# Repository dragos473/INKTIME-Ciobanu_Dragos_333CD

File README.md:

# InkTime – Smartwatch Open Source

InkTime este un smartwatch open-source construit in jurul microcontroller-ului nRF52840. Are display e-paper de 1.54", feedback haptic, si incarcare prin USB-C.

## Diagrama Bloc

```
                         +-----------+
        USB-C ──VBUS──>──| BQ25180   |──VBAT──>──[ Baterie LiPo ]
        (J3)             | (Charger) |              |
          |              +-----------+               |
          |                   |                      |
          |                   v                      v
          |              +-----------+         +-----------+
          |              | RT6160A   |<──VREG──| MAX17048  |
          |              | (DC/DC)   |         | (Fuel     |
          |              +-----------+         |  Gauge)   |
          |                   |                +-----------+
          |                 3V3                      |
          |                   |                   ALERT
          v                   v                      |
     +--------------------------------------------+  |
     |               nRF52840                      |<-+
     |                                             |
     |   SPI ──> Display E-Paper (conector FPC J2) |
     |   I2C ──> BMA423 (IMU)                      |
     |   I2C ──> DRV2605 (Haptic Driver)           |
     |   I2C ──> BQ25180 / RT6160A / MAX17048      |
     |   GPIO ──> 3x Butoane (UP/ENTER/DOWN)       |
     |   USB ──> USB-C (D+/D-)                     |
     |   RF ──> Antena 2.4GHz (BLE)                |
     +---------------------------------------------+
```

## Descriere Hardware

### Microcontroller – nRF52840

nRF52840 e IC-ul principal al proiectului. E un SoC cu procesor Cortex-M4F, are 1MB flash si 256kB RAM si merge pana la 64MHz. Suporta BLE 5.0 si USB 2.0. Toate perifericele de pe placa comunica cu el prin I2C, SPI sau GPIO.

### Alimentare

Lantul de alimentare arata asa: USB-C (VBUS, 5V) → BQ25180 (incarcator LiPo) → baterie LiPo (VBAT) → RT6160A (convertor DC/DC buck-boost) → linia de 3V3.

### Display E-Paper

Display-ul se conecteaza printr-un conector FPC cu 24 de pini. Circuitul de drive pentru e-paper foloseste un boost converter ca sa genereze tensiunile mari (PREVGH si PREVGL) de care are nevoie panoul. Un P-MOSFET (DMG2305UX) controlat de pinul P1.01 porneste/opreste alimentarea circutului de display, ca sa poata fi oprit complet cand nu se face refresh.

Semnalele SPI (SCK, MOSI, CS) si GPIO-urile de control (DC, RST, BUSY) merg direct la nRF52840. Fiecare linie de tensiune mare are condensatoare de decuplare de 1µF/50V.

### IMU – BMA423

BMA423 e un accelerometru triaxial folosit pentru numararea pasilor si detectarea gesturilor. Comunica pe I2C. Pinul SDO e legat la GND printr-un rezistor de 0Ω (R3), ceea ce seteaza adresa I2C la 0x18. CSB e legat la VDD ca sa selecteze modul I2C. INT1 si INT2 merg la nRF52840 pentru interrupt-uri.

### Haptic Driver – DRV2605

DRV2605 controleaza un motor LRA/ERM pentru feedback haptic. E controlat prin I2C si activat prin GPIO (P0.12 → EN). Pinul IN/TRIG e legat la GND (nu se foloseste in modul I2C). OUT+ si OUT- se conecteaza la motor prin test pad-uri.

### USB-C si Protectie ESD

Conectorul USB-C (KH-TYPE-C-16P) furnizeaza alimentare (VBUS) si date (D+, D-). Doua rezistoare de 5.1kΩ pe CC1 si CC2 identifica dispozitivul ca UFP (sink). USBLC6-2SC6Y asigura protectie ESD pe liniile de date. D+/D- se conecteaza la controller-ul USB intern al nRF52840.

### Butoane

Trei butoane tactile (EVP-AKE31A): UP (P0.13), ENTER (P0.14), DOWN (P1.02). Fiecare buton are un pull-up de 10kΩ la 3V3 si un condensator de debounce de 1µF la GND. Cand e apasat, butonul trage pinul la GND (active-low).

### Debug SWD

Un footprint TC2030-IDC (tag-connect) ofera acces SWD (SWDIO, SWDCLK, RESET, VCC, GND). Pe placa sunt si test pad-uri pentru SWO, SWDIO, SWDCLK, RESET, 3V3 si GND.

### Magistrala I2C

Toate perifericele I2C sunt pe acelasi bus, pe pinii P0.06 (SDA) si P0.07 (SCL). Rezistoarele de pull-up sunt de 3.3kΩ, conectate la 3V3.

| Dispozitiv | Adresa I2C | Functie |
|------------|------------|---------|
| BQ25180 | 0x6A | Incarcator baterie |
| RT6160A | 0x75 | Convertor DC/DC |
| MAX17048 | 0x36 | Fuel gauge |
| BMA423 | 0x18 | Accelerometru |
| DRV2605 | 0x5A | Driver haptic |

## Pinii nRF52840

| Pin | Pad | Semnal | Descriere |
|-----|-----|--------|-----------|
| P0.00 | D2 | XL1 | Intrare cristal 32.768kHz |
| P0.01 | F2 | XL2 | Iesire cristal 32.768kHz |
| P0.02 | A12 | SCK | SPI clock catre display e-paper |
| P0.03 | B13 | MOSI | SPI data catre display e-paper |
| P0.05 | K2 | EPD_CS | SPI chip select pentru display |
| P0.06 | L1 | SDA | I2C data (bus comun) |
| P0.07 | M2 | SCL | I2C clock (bus comun) |
| P0.08 | N1 | IMU_INT1 | Interrupt 1 de la BMA423 |
| P0.10 | J24 | ALERT | Alerta baterie de la MAX17048 |
| P0.11 | T2 | PMIC_INT | Interrupt de la BQ25180 |
| P0.12 | U1 | HAPTIC_EN | Enable pentru DRV2605 |
| P0.13 | AD8 | BTN_UP | Buton UP (active-low) |
| P0.14 | AC9 | BTN_ENTER | Buton ENTER (active-low) |
| P0.15 | AD10 | EPD_DC | Data/Command pentru display |
| P0.16 | AC11 | EPD_RST | Reset display e-paper |
| P0.17 | AD12 | EPD_BUSY | Busy flag display e-paper |
| P0.18 | AC13 | RESET | Reset sistem |
| P1.00 | AD22 | SWO | Serial Wire Output (debug) |
| P1.01 | Y23 | PWR_EPD | Gate MOSFET alimentare display |
| P1.02 | W24 | BTN_DOWN | Buton DOWN (active-low) |
| P1.08 | P2 | IMU_INT2 | Interrupt 2 de la BMA423 |
| AD2 | — | VBUS | Detectie USB VBUS |
| AD4 | — | D- | USB data minus |
| AD6 | — | D+ | USB data plus |
| AA24 | — | SWDCLK | SWD clock (debug) |
| AC24 | — | SWDIO | SWD data (debug) |
| XC1/B24 | — | XC1 | Intrare cristal 32MHz |
| XC2/A23 | — | XC2 | Iesire cristal 32MHz |
| H23 | — | ANT | Iesire RF catre antena |
| W1, B1, A22, AD14, AD23 | — | VDD | Alimentare 3.3V |
| Y2 | — | VDDH | Alimentare 3.3V (high-voltage) |
| B7, F23 | — | VSS/GND | Masa |

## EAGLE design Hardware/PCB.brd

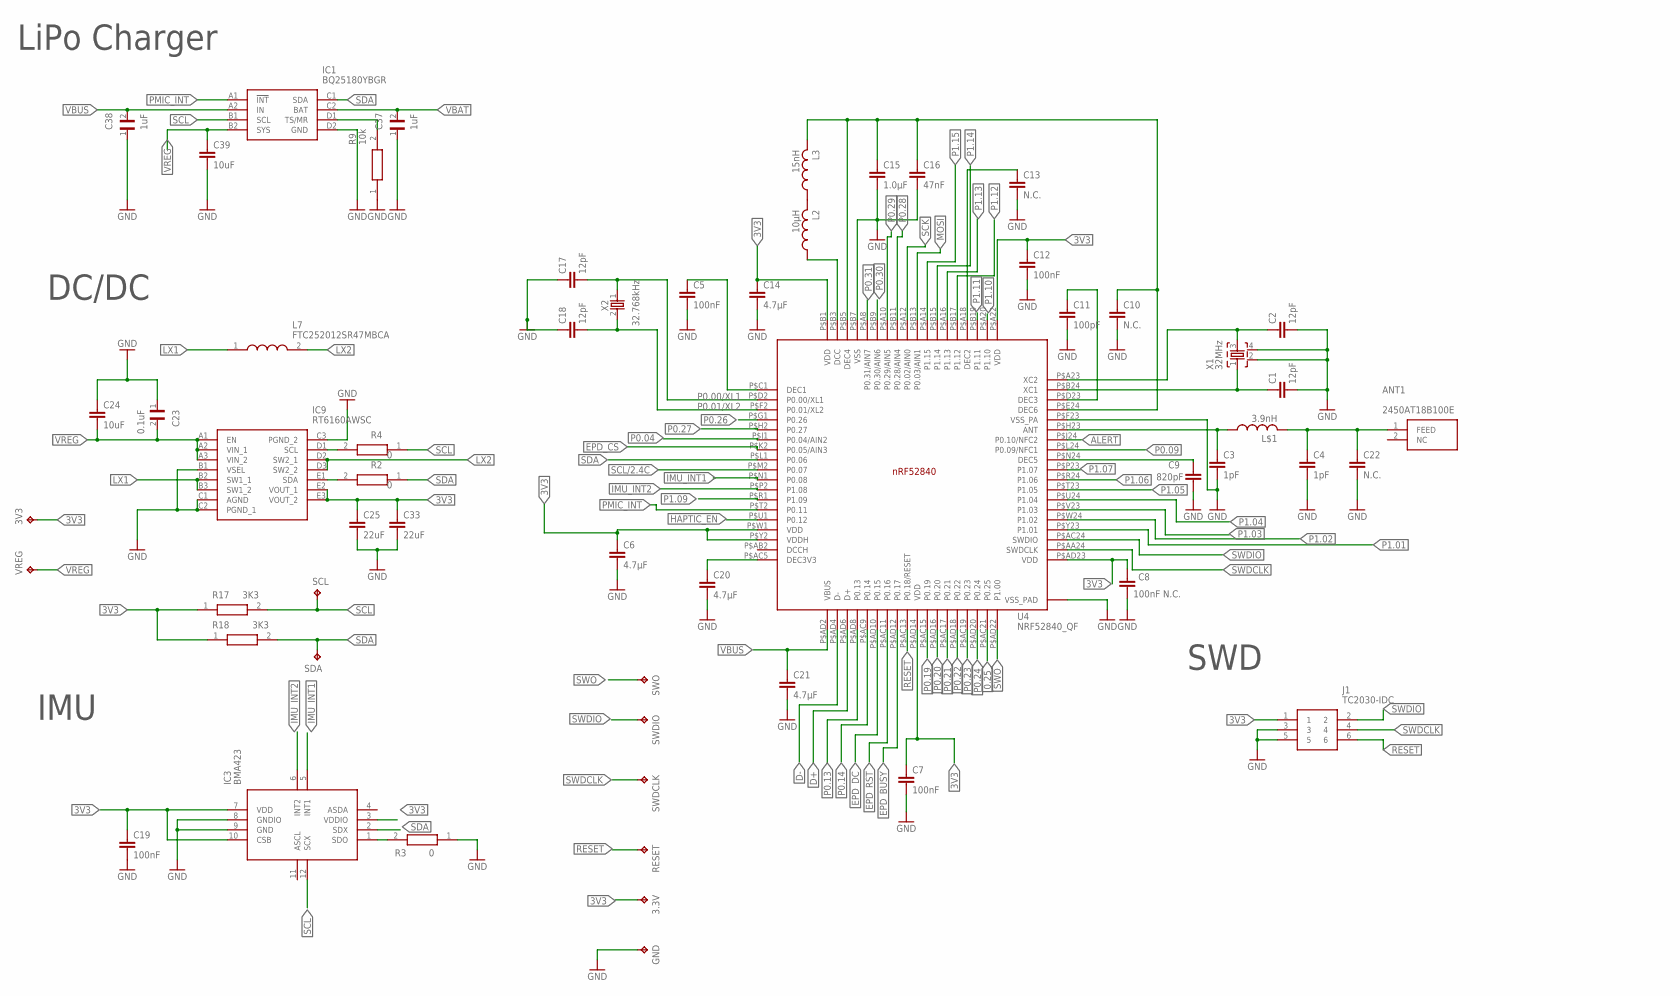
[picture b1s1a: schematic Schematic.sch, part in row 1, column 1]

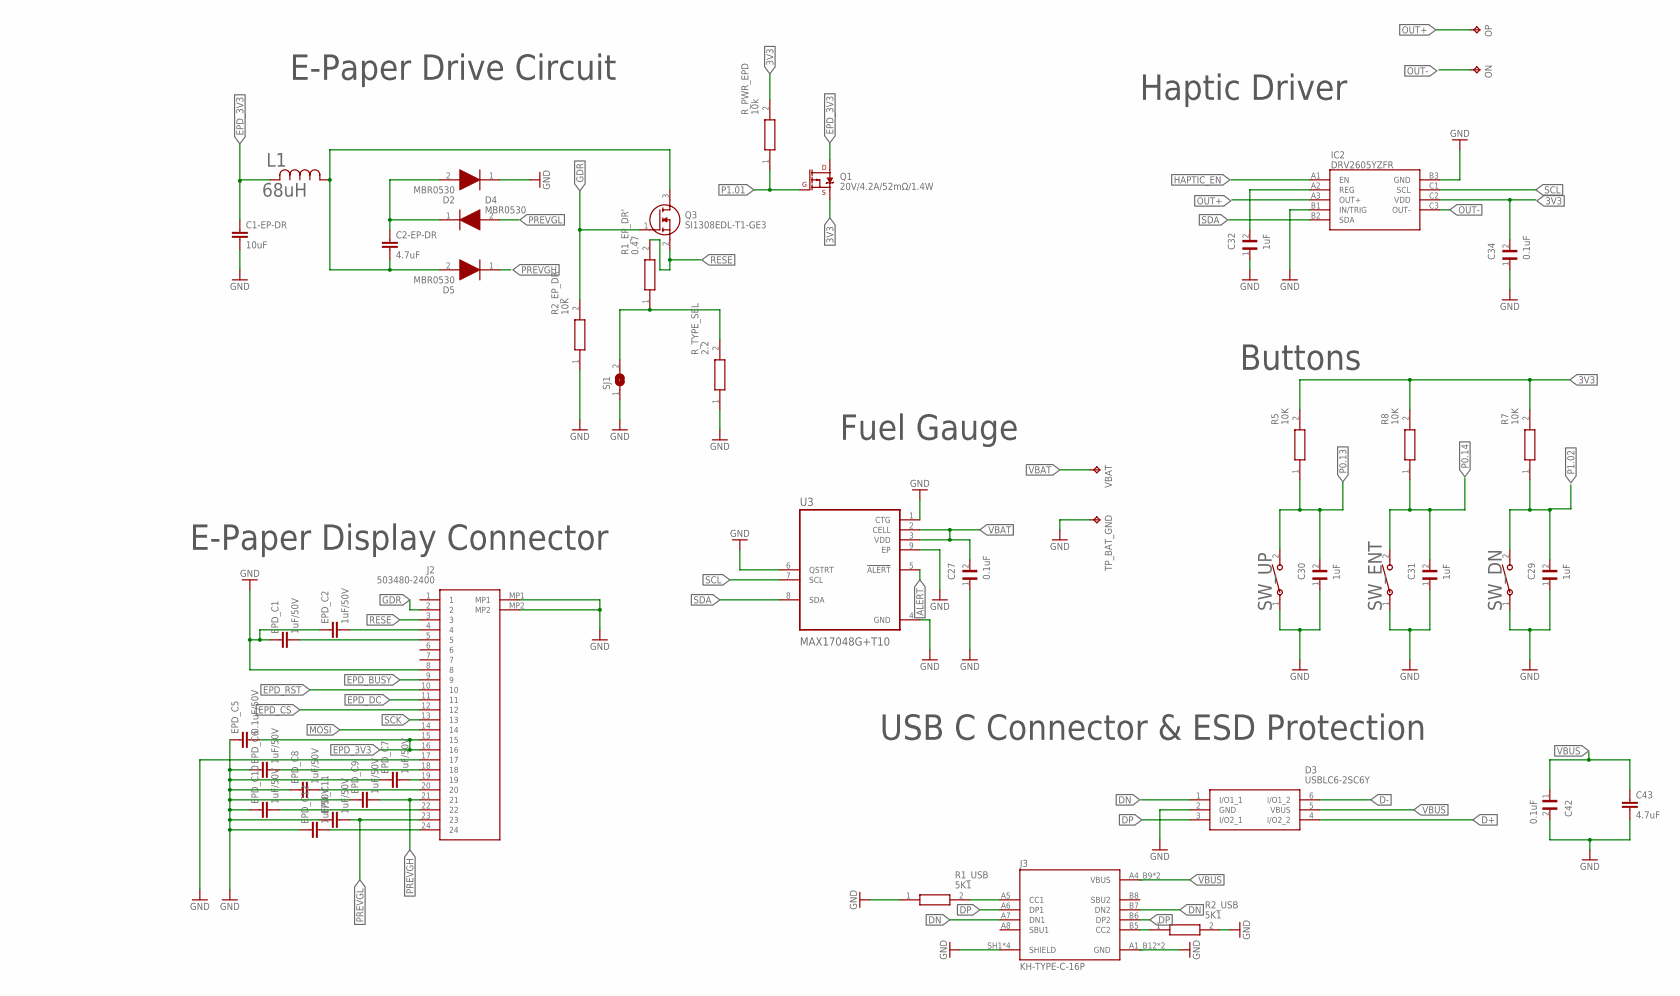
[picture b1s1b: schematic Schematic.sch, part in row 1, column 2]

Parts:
3.3V, 3V3: HECTOR_WATCH_1_TPTP20R; HECTOR_WATCH_1_TP20R
ANT1: 2450AT18B100E; 2450AT18B100E_ANTC3216X140N
C1, C2, C17, C18: 12pF; NORDIC_NRF_3_RESC0201_L
C1-EP-DR, C24, C39: 10uF; NORDIC_NRF_3_RESC0201_L
C2-EP-DR, C43: 4.7uF; NORDIC_NRF_3_RESC0201_L
C3, C4: 1pF; NORDIC_NRF_3_RESC0201_L
C5, C7, C12, C19: 100nF; NORDIC_NRF_3_RESC0201_L
C6, C14, C20, C21: 4.7μF; NORDIC_NRF_3_RESC0201_L
C8: 100nF N.C.; NORDIC_NRF_3_RESC0201_L
C9: 820pF; NORDIC_NRF_3_RESC0201_L
C10, C13, C22: N.C.; NORDIC_NRF_3_RESC0201_L
C11: 100pF; NORDIC_NRF_3_RESC0201_L
C15: 1.0μF; NORDIC_NRF_3_RESC0201_L
C16: 47nF; NORDIC_NRF_3_RESC0201_L
C23, C27, C34, C42: 0.1uF; GRM011R60J152KE01L_2_CAPC0201X13N
C25, C33: 22uF; NORDIC_NRF_3_RESC0201_L
C29, C30, C31, C32, C37, C38: 1uF; GRM011R60J152KE01L_2_CAPC0201X13N
D2, D4, D5: MBR0530; ESP32_C6_LIBRARY_5_SOD3716X135N
D3: USBLC6-2SC6Y; ESP32_C6_LIBRARY_3_SOT95P280X145-6N
EPD_C1, EPD_C2, EPD_C6, EPD_C7, EPD_C8, EPD_C9, EPD_C10, EPD_C11, EPD_C12: 1uF/50V; NORDIC_NRF_3_RESC0201_L
EPD_C5: 0.1uF/50V; NORDIC_NRF_3_RESC0201_L
GND: HECTOR_WATCH_1_TPTP20R; HECTOR_WATCH_1_TP20R
IC1: BQ25180YBGR; BQ25180YBGR_BGA8C40P2X4_100X155X50
IC2: DRV2605YZFR; DRV2605YZFR_BGA9C50P3X3_144X144X62
IC3: BMA423; BMA423_BMA423
IC9: RT6160AWSC; RT6160AWSC_BGA15C40P3X5_140X230X60
J1: TC2030-IDC; TC2030-IDC_TC2030IDC
J2: 503480-2400; 503480-2400_5034802400
J3: KH-TYPE-C-16P; KH-TYPE-C-16P_KINGHELM_KH-TYPE-C-16P
L1: 68uH; ESP32_C6_LIBRARY_2_IND_4828-WE-TPC_WRE
L2: 10μH; NORDIC_NRF_2_RESC0201_L
L3: 15nH; NORDIC_NRF_2_RESC0201_L
L7: FTC252012SR47MBCA; MLP2016SR47MT0S1_INDC2016X100N
L$1: 3.9nH; NORDIC_NRF_2_RESC0402_L
ON: HECTOR_WATCH_1_TPTP20R; HECTOR_WATCH_1_TP20R
OP: HECTOR_WATCH_1_TPTP20R; HECTOR_WATCH_1_TP20R
Q1: 20V/4.2A/52mΩ/1.4W; ESP32_C6_LIBRARY_4_ESP32_C6_LIBRARY_4_ESP32_C6_LIBRARY_4_ES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
Q3: SI1308EDL-T1-GE3; ESP32_C6_LIBRARY_6_SOT65P210X110-3N
R1_EP_DR': 0.47; ERA-1AEB3401C_0201
R1_USB, R2_USB: 5K1; ERA-1AEB3401C_0201
R2, R3, R4: 0; ERA-1AEB3401C_0201
R2_EP_DR, R5, R7, R8: 10K; ERA-1AEB3401C_0201
R9: 10k; CPF0201D7K68C1_0201
R17, R18: 3K3; ERA-1AEB3401C_0201
RESET: HECTOR_WATCH_1_TPTP20R; HECTOR_WATCH_1_TP20R
R_PWR_EPD: 10k; ERA-1AEB3401C_0201
R_TYPE_SEL: 2.2; ERA-1AEB3401C_0201
SCL: HECTOR_WATCH_1_TPTP20R; HECTOR_WATCH_1_TP20R
SDA: HECTOR_WATCH_1_TPTP20R; HECTOR_WATCH_1_TP20R
SJ1: ESP32_C6_LIBRARY_7_JUMPER_SJ
SWDCLK: HECTOR_WATCH_1_TPTP20R; HECTOR_WATCH_1_TP20R
SWDIO: HECTOR_WATCH_1_TPTP20R; HECTOR_WATCH_1_TP20R
SWO: HECTOR_WATCH_1_TPTP20R; HECTOR_WATCH_1_TP20R
SW_DN: 2025-10-22_07-23-44_LIBRARY_EVP-AKE31ASW_EVP-AKE3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; 2025-10-22_07-23-44_LIBRARY_SW_EVP-AKE31A_PAN
SW_ENT: 2025-10-22_07-23-44_LIBRARY_EVP-AKE31ASW_EVP-AKE3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; 2025-10-22_07-23-44_LIBRARY_SW_EVP-AKE31A_PAN
SW_UP: 2025-10-22_07-23-44_LIBRARY_EVP-AKE31ASW_EVP-AKE3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; 2025-10-22_07-23-44_LIBRARY_SW_EVP-AKE31A_PAN
TP_BAT_GND: HECTOR_WATCH_1_TPTP20R; HECTOR_WATCH_1_TP20R
U3: MAX17048G+T10; ESP32_C6_LIBRARY_SON50P200X200X80-9N
U4: NRF52840_QF; NORDIC_NRF_4_AQFN50P700X700X85_HS-74N
VBAT: HECTOR_WATCH_1_TPTP20R; HECTOR_WATCH_1_TP20R
VREG: HECTOR_WATCH_1_TPTP20R; HECTOR_WATCH_1_TP20R
X1: 32MHz; NORDIC_NRF_BT-XTAL_2016_N
X2: 32.768kHz; NORDIC_NRF_1_XTAL_3215_N

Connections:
0.25: U4.P$AC21 (P0.25)
3V3: 3.3V.TP, 3V3.TP, C6.1, C7.1, C8.1, C12.1, C14.1, C19.1, C25.1, C33.1, C34.2, IC2.C2 (VDD), IC3.3 (VDDIO), IC3.7 (VDD), IC3.10 (CSB), IC9.E2 (VOUT_1), IC9.E3 (VOUT_2), J1.1, Q1.2 (S), R5.2, R7.2, R8.2, R17.1, R18.1, R_PWR_EPD.2, U4.P$A22 (VDD), U4.P$AD14 (VDD), U4.P$AD23 (VDD), U4.P$B1 (VDD), U4.P$W1 (VDD), U4.P$Y2 (VDDH)
ALERT: U3.5 (!ALERT), U4.P$J24 (P0.10/NFC2)
D+: D3.4 (I/O2_2), U4.P$AD6 (D+)
D-: D3.6 (I/O1_2), U4.P$AD4 (D-)
DN: D3.1 (I/O1_1), J3.A7 (DN1), J3.B7 (DN2)
DP: D3.3 (I/O2_1), J3.A6 (DP1), J3.B6 (DP2)
EPD_3V3: C1-EP-DR.1, EPD_C5.2, J2.15, J2.16, L1.2, Q1.3 (D)
EPD_BUSY: J2.9, U4.P$AD12 (P0.17)
EPD_CS: J2.12, U4.P$K2 (P0.05/AIN3)
EPD_DC: J2.11, U4.P$AD10 (P0.15)
EPD_RST: J2.10, U4.P$AC11 (P0.16)
GDR: J2.2, Q3.1 (G), R2_EP_DR.2
GND: C1.2, C1-EP-DR.2, C2.2, C3.2, C4.2, C5.2, C6.2, C7.2, C8.2, C9.2, C10.2, C11.2, C12.2, C13.2, C14.2, C15.2, C16.2, C17.1, C18.1, C19.2, C20.2, C21.2, C22.2, C23.1, C24.1, C25.2, C27.1, C29.1, C30.1, C31.1, C32.1, C33.2, C34.1, C37.1, C38.1, C39.2, C42.2, C43.2, D2.1 (K), D3.2 (GND), EPD_C1.1, EPD_C2.1, EPD_C5.1, EPD_C6.1, EPD_C7.1, EPD_C8.1, EPD_C9.1, EPD_C10.1, EPD_C11.1, EPD_C12.1, GND.TP, IC1.D2 (GND), IC2.B1 (IN/TRIG), IC2.B3 (GND), IC3.8 (GNDIO), IC3.9 (GND), IC9.B1 (VSEL), IC9.C1 (AGND), IC9.C2 (PGND_1), IC9.C3 (PGND_2), J1.3, J1.5, J2.8, J2.17, J2.MP1, J2.MP2, J3.A1_B12 (GND), J3.A12_B1 (GND), J3.SH1 (SHIELD), J3.SH2 (SHIELD), J3.SH3 (SHIELD), J3.SH4 (SHIELD), R1_USB.1, R2_EP_DR.1, R2_USB.2, R3.1, R9.1, R_TYPE_SEL.1, SJ1.1, SW_DN.1, SW_ENT.1, SW_UP.1, TP_BAT_GND.TP, U3.1 (CTG), U3.4 (GND), U3.6 (QSTRT), U3.9 (EP), U4.P$74 (VSS_PAD), U4.P$75 (VSS_PAD), U4.P$76 (VSS_PAD), U4.P$77 (VSS_PAD), U4.P$78 (VSS_PAD), U4.P$79 (VSS_PAD), U4.P$80 (VSS_PAD), U4.P$81 (VSS_PAD), U4.P$82 (VSS_PAD), U4.P$83 (VSS_PAD), U4.P$84 (VSS_PAD), U4.P$85 (VSS_PAD), U4.P$86 (VSS_PAD), U4.P$87 (VSS_PAD), U4.P$88 (VSS_PAD), U4.P$89 (VSS_PAD), U4.P$90 (VSS_PAD), U4.P$B7 (VSS), U4.P$F23 (VSS_PA), X1.2, X1.4
HAPTIC_EN: IC2.A1 (EN), U4.P$U1 (P0.12)
IMU_INT1: IC3.5 (INT1), U4.P$N1 (P0.08)
IMU_INT2: IC3.6 (INT2), U4.P$P2 (P1.08)
LX1: IC9.B2 (SW1_1), IC9.B3 (SW1_2), L7.1
LX2: IC9.D2 (SW2_1), IC9.D3 (SW2_2), L7.2
MOSI: J2.14, U4.P$B13 (P0.03/AIN1)
unnamed: IC1.D1 (TS/MR), R9.2
unnamed: IC9.D1 (SCL), R4.2
unnamed: IC9.E1 (SDA), R2.2
unnamed: C5.1, U4.P$C1 (DEC1)
unnamed: C20.1, U4.P$AC5 (DEC3V3)
unnamed: C9.1, U4.P$N24 (DEC5)
unnamed: C3.1, L$1.1, U4.P$H23 (ANT)
unnamed: ANT1.1 (FEED), C4.1, C22.1, L$1.2
unnamed: C2.1, U4.P$A23 (XC2), X1.3
unnamed: C1.1, U4.P$B24 (XC1), X1.1
unnamed: C10.1, C15.1, C16.1, L3.2, U4.P$B5 (DEC4), U4.P$E24 (DEC6)
unnamed: C11.1, U4.P$D23 (DEC3)
unnamed: C13.1, U4.P$A18 (DEC2)
unnamed: L2.2, L3.1
unnamed: L2.1, U4.P$B3 (DCC)
unnamed: IC3.1 (SDO), R3.2
unnamed: C2-EP-DR.2, D5.2 (A), L1.1, Q3.3 (D)
unnamed: C2-EP-DR.1, D2.2 (A), D4.1 (K)
unnamed: R1_EP_DR'.1, R_TYPE_SEL.2, SJ1.2
unnamed: C32.2, IC2.A2 (REG)
unnamed: EPD_C2.2, J2.4
unnamed: EPD_C1.2, J2.5
unnamed: EPD_C6.2, J2.18
unnamed: EPD_C7.2, J2.19
unnamed: EPD_C8.2, J2.20
unnamed: EPD_C10.2, J2.22
unnamed: EPD_C12.2, J2.24
unnamed: J3.B5 (CC2), R2_USB.1
unnamed: J3.A5 (CC1), R1_USB.2
OUT+: IC2.A3 (OUT+), OP.TP
OUT-: IC2.C3 (OUT-), ON.TP
P0.00/XL1: C17.2, U4.P$D2 (P0.00/XL1), X2.1
P0.01/XL2: C18.2, U4.P$F2 (P0.01/XL2), X2.2
P0.04: U4.P$J1 (P0.04/AIN2)
P0.09: U4.P$L24 (P0.09/NFC1)
P0.13: C30.2, R5.1, SW_UP.2, U4.P$AD8 (P0.13)
P0.14: C31.2, R8.1, SW_ENT.2, U4.P$AC9 (P0.14)
P0.19: U4.P$AC15 (P0.19)
P0.20: U4.P$AD16 (P0.20)
P0.21: U4.P$AC17 (P0.21)
P0.22: U4.P$AD18 (P0.22)
P0.23: U4.P$AC19 (P0.23)
P0.24: U4.P$AD20 (P0.24)
P0.26: U4.P$G1 (P0.26)
P0.27: U4.P$H2 (P0.27)
P0.28: U4.P$B11 (P0.28/AIN4)
P0.29: U4.P$A10 (P0.29/AIN5)
P0.30: U4.P$B9 (P0.30/AIN6)
P0.31: U4.P$A8 (P0.31/AIN7)
P1.01: Q1.1 (G), R_PWR_EPD.1, U4.P$Y23 (P1.01)
P1.02: C29.2, R7.1, SW_DN.2, U4.P$W24 (P1.02)
P1.03: U4.P$V23 (P1.03)
P1.04: U4.P$U24 (P1.04)
P1.05: U4.P$T23 (P1.05)
P1.06: U4.P$R24 (P1.06)
P1.07: U4.P$P23 (P1.07)
P1.09: U4.P$R1 (P1.09)
P1.10: U4.P$A20 (P1.10)
P1.11: U4.P$B19 (P1.11)
P1.12: U4.P$B17 (P1.12)
P1.13: U4.P$A16 (P1.13)
P1.14: U4.P$B15 (P1.14)
P1.15: U4.P$A14 (P1.15)
PMIC_INT: IC1.A1 (!INT), U4.P$T2 (P0.11)
PREVGH: D5.1 (K), EPD_C9.2, J2.21
PREVGL: D4.2 (A), EPD_C11.2, J2.23
RESE: J2.3, Q3.2 (S), R1_EP_DR'.2
RESET: J1.6, RESET.TP, U4.P$AC13 (P0.18/RESET)
SCK: J2.13, U4.P$A12 (P0.02/AIN0)
SCL: IC1.B1 (SCL), IC2.C1 (SCL), IC3.12 (SCX), R4.1, R17.2, SCL.TP, U3.7 (SCL)
SCL/2.4C: U4.P$M2 (P0.07)
SDA: IC1.C1 (SDA), IC2.B2 (SDA), IC3.2 (SDX), R2.1, R18.2, SDA.TP, U3.8 (SDA), U4.P$L1 (P0.06)
SWDCLK: J1.4, SWDCLK.TP, U4.P$AA24 (SWDCLK)
SWDIO: J1.2, SWDIO.TP, U4.P$AC24 (SWDIO)
SWO: SWO.TP, U4.P$AD22 (P1.00)
VBAT: C27.2, C37.2, IC1.C2 (BAT), U3.2 (CELL), U3.3 (VDD), VBAT.TP
VBUS: C21.1, C38.2, C42.1, C43.1, D3.5 (VBUS), IC1.A2 (IN), J3.A4_B9 (VBUS), J3.A9_B4 (VBUS), U4.P$AD2 (VBUS)
VREG: C23.2, C24.2, C39.1, IC1.B2 (SYS), IC9.A1 (EN), IC9.A2 (VIN_1), IC9.A3 (VIN_2), VREG.TP

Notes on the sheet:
LiPo Charger
DC/DC
IMU
SWD
E-Paper Drive Circuit
E-Paper Display Connector
Fuel Gauge
Haptic Driver
Buttons
USB C Connector & ESD Protection

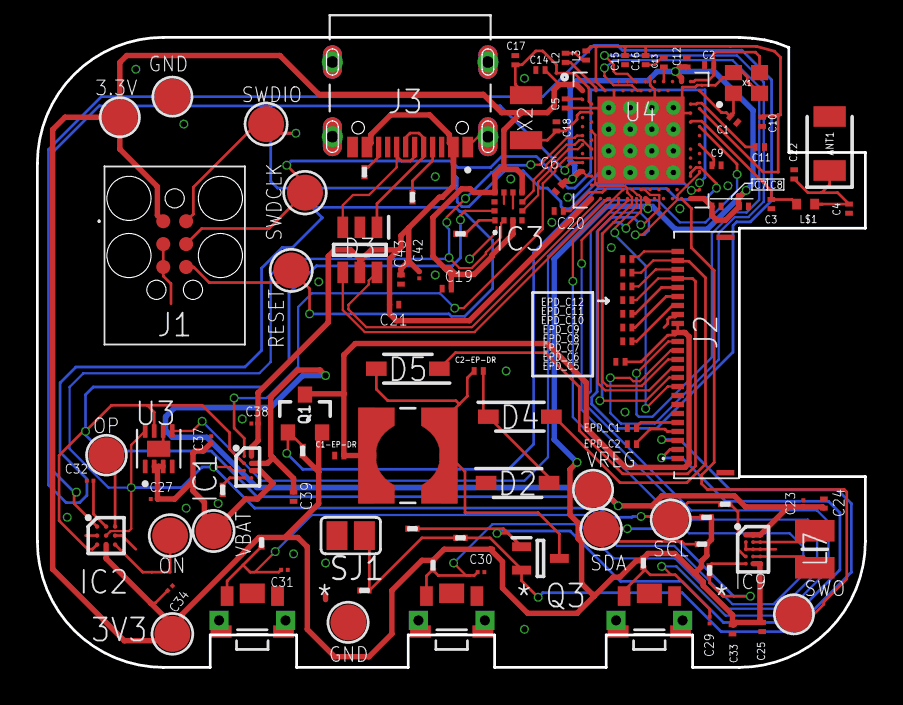
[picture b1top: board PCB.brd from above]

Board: 2 copper layers, 46.0 x 35.0 mm, 105 parts (0 on the bottom side), 70 nets.

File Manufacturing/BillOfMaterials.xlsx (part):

Reference Designators | Quantity | Description | Datasheet | Purchase Link | Package | Value | Manufacturer | Manufacturer Part Number | Vendor | Vendor Part Number | Top/Bottom
 | 1 | PCB Board |  |  | Board
3.3V, 3V3, GND, ON, OP, RESET, SCL, SDA, SWDCLK, SWDIO, SWO, TP_BAT_GND, VBAT, 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 | 14 | Test pad |  |  | HECTOR_WATCH_1_TP20R | HECTOR_WATCH_1_TPTP20R |  |  |  |  | Top
ANT1 | 1 | Antennas 2.45GHz ANTENNA | READ_DATASHEET | BUY_PART | 2450AT18B100E_ANTC3216X140N | 2450AT18B100E | Johanson Technology | 2450AT18B100E | LCSC | C2836414 | Top | https://www.johansontechnology.com/docs/1187/2450AT18B100_X8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 | https://jlcpcb.com/partdetail/C2836414
C1, C2, C17, C18 | 4 | Generic chip capacitor | READ_DATASHEET | BUY_PART | NORDIC_NRF_3_RESC0201_L | 12pF | Murata | GRM0335C1H120JA01D | LCSC | C106295 | Top | https://www.murata.com/ | https://jlcpcb.com/partdetail/C106295
C1-EP-DR, C24, C39 | 3 | Generic chip capacitor | READ_DATASHEET |  | NORDIC_NRF_3_RESC0201_L | 10uF | Murata | GRM155R60J106ME15 |  |  | Top | https://device.report/manual/8918227
C2-EP-DR, C43 | 2 | Generic chip capacitor |  |  | NORDIC_NRF_3_RESC0201_L | 4.7uF |  |  |  |  | Top
C3, C4 | 2 | Generic chip capacitor |  |  | NORDIC_NRF_3_RESC0201_L | 1pF |  |  |  |  | Top
C5, C7, C12, C19 | 4 | Generic chip capacitor |  |  | NORDIC_NRF_3_RESC0201_L | 100nF | Murata | GRM033R60J104KE19D |  |  | Top
C6, C14, C20, C21 | 4 | Generic chip capacitor |  |  | NORDIC_NRF_3_RESC0201_L | 4.7μF |  |  |  |  | Top
C8 | 1 | Generic chip capacitor |  |  | NORDIC_NRF_3_RESC0201_L | 100nF N.C. |  |  |  |  | Top
C9 | 1 | Generic chip capacitor |  |  | NORDIC_NRF_3_RESC0201_L | 820pF |  |  |  |  | Top
C10, C13, C22 | 3 | Generic chip capacitor |  |  | NORDIC_NRF_3_RESC0201_L | N.C. |  |  |  |  | Top
C11 | 1 | Generic chip capacitor |  |  | NORDIC_NRF_3_RESC0201_L | 100pF |  |  |  |  | Top
C15 | 1 | Generic chip capacitor |  |  | NORDIC_NRF_3_RESC0201_L | 1.0μF |  |  |  |  | Top
C16 | 1 | Generic chip capacitor |  |  | NORDIC_NRF_3_RESC0201_L | 47nF |  |  |  |  | Top
C23, C27, C34, C42 | 4 | Check availability |  |  | CAPC0201X13N | 0.1uF |  |  |  |  | Top
C25, C33 | 2 | Generic chip capacitor |  |  | NORDIC_NRF_3_RESC0201_L | 22uF | Murata | GRM188R61A226ME15D |  |  | Top
C29, C30, C31, C32, C37, C38 | 6 | Check availability |  |  | CAPC0201X13N | 1uF |  |  |  |  | Top
D2, D4, D5 | 3 | ON SEMICONDUCTOR - MBR0530 - DIODE, SCHOTTKY, 0.5A, 30V, SOD-123 | READ_DATASHEET | BUY_PART | SOD3716X135N | MBR0530 | ON Semiconductor | MBR0530 | LCSC | C475718 | Top | https://www.onsemi.com/pdf/datasheet/mbr0530-d.pdf | https://jlcpcb.com/partdetail/C475718
D3 | 1 | Low Cap. ESD Protection Auto SOT-23-6 STMicroelectronics USBLC6-2SC6Y, Dual Uni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 | READ_DATASHEET | BUY_PART | SOT95P280X145-6N | USBLC6-2SC6Y | STMicroelectronics | USBLC6-2SC6Y | LCSC | C323793 | Top | https://www.st.com/resource/en/datasheet/usblc6-2sc6y.pdf | https://jlcpcb.com/partdetail/C323793
EPD_C1, EPD_C2, EPD_C6, EPD_C7, EPD_C8, EPD_C9, EPD_C10, EPD_C11, EPD_C12 | 9 | Generic chip capacitor |  |  | NORDIC_NRF_3_RESC0201_L | 1uF/50V |  |  |  |  | Top
EPD_C5 | 1 | Generic chip capacitor |  |  | NORDIC_NRF_3_RESC0201_L | 0.1uF/50V |  |  |  |  | Top
IC1 | 1 | Charger IC Lithium Ion/Polymer, Lithium Iron Phosphate 8-DSBGA (1.6x1.1) | READ_DATASHEET | BUY_PART | BQ25180YBGR_BGA8C40P2X4_100X155X50 | BQ25180YBGR | Texas Instruments | BQ25180YBGR | LCSC | C3682423 | Top | https://www.ti.com/lit/ds/symlink/bq25180.pdf | https://jlcpcb.com/partdetail/C3682423
IC2 | 1 | Haptic Driver for ERM/LRA with Built-In Library and Smart Loop Architecture | READ_DATASHEET | BUY_PART | DRV2605YZFR_BGA9C50P3X3_144X144X62 | DRV2605YZFR | Texas Instruments | DRV2605YZFR | LCSC | C81079 | Top | https://www.ti.com/lit/ds/symlink/drv2605.pdf | https://jlcpcb.com/partdetail/C81079
IC3 | 1 | Accelerometers Triaxial low-g 12bit Acceleration Sensor | READ_DATASHEET | BUY_PART | BMA423_BMA423 | BMA423 | Bosch Sensortec | BMA423 | LCSC | C189517 | Top | https://mm.digikey.com/Volume0/opasdata/d220001/medias/docus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 | https://jlcpcb.com/partdetail/C189517
IC9 | 1 | Buck-Boost Regulator Positive Output Step-Up/Step-Down I2C DC-DC Controller IC 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 | READ_DATASHEET | BUY_PART | RT6160AWSC_BGA15C40P3X5_140X230X60 | RT6160AWSC | Richtek | RT6160AWSC | LCSC | C3028302 | Top | https://www.richtek.com/m/~/media/EVB%20PDF%20File/EVB_RT616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 | https://jlcpcb.com/partdetail/C3028302
J1 | 1 | CABLE ADAPTER 6 POS | READ_DATASHEET |  | TC2030-IDC_TC2030IDC | TC2030-IDC | Tag-Connect | TC2030-IDC |  |  | Top | https://www.tag-connect.com/wp-content/uploads/bsk-pdf-manag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
J2 | 1 | FFC & FPC Connectors 0.5mm FPC RA SMT Dual Contact 24Ckt | READ_DATASHEET | BUY_PART | 503480-2400_5034802400 | 503480-2400 | Molex | 503480-2400 | LCSC | C234192 | Top | https://www.molex.com/content/dam/molex/molex-dot-com/en_us/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 | https://jlcpcb.com/partdetail/C234192
J3 | 1 | Check availability | READ_DATASHEET | BUY_PART | KINGHELM_KH-TYPE-C-16P | KH-TYPE-C-16P | Shenzhen Kinghelm | KH-TYPE-C-16P | LCSC | C709357 | Top | https://datasheet.lcsc.com/lcsc/2304140030_Shenzhen-Kinghelm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 | https://jlcpcb.com/partdetail/C709357
L$1 | 1 | Generic chip inductor |  |  | NORDIC_NRF_2_RESC0402_L | 3.9nH |  |  |  |  | Top
L1 | 1 |  |  |  | ESP32_C6_LIBRARY_2_IND_4828-WE-TPC_WRE | 68uH |  |  |  |  | Top
L2 | 1 | Generic chip inductor |  |  | NORDIC_NRF_2_RESC0201_L | 10μH |  |  |  |  | Top
L3 | 1 | Generic chip inductor |  |  | NORDIC_NRF_2_RESC0201_L | 15nH |  |  |  |  | Top
L7 | 1 | SMD / SMT Inductors (Coils), L=0.47?H, L x W x T : |  | BUY_PART | MLP2016SR47MT0S1_INDC2016X100N | FTC252012SR47MBCA | Changjiang | FTC252012SR47MBCA | LCSC | C5832368 | Top |  | https://jlcpcb.com/partdetail/C5832368
Q1 | 1 | P-channel MOSFETs | READ_DATASHEET | BUY_PART | ESP32_WROVER_SPARKFUN-DISCRETESEMI_SOT23-3 | 20V/4.2A/52mΩ/1.4W | AOS | AO3401A | LCSC | C15127 | Top | https://aosmd.com/res/data_sheets/AO3401A.pdf | https://jlcpcb.com/partdetail/C15127
Q3 | 1 | MOSFET N-Ch 30V 1.5A TrenchFET SC70 Vishay Si1308EDL-T1-GE3 N-channel MOSFET Tr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 | READ_DATASHEET | BUY_PART | SOT65P210X110-3N | SI1308EDL-T1-GE3 | Vishay Siliconix | SI1308EDL-T1-GE3 | LCSC | C7603347 | Top | https://www.vishay.com/doc/?63399 | https://jlcpcb.com/partdetail/C7603347
R_PWR_EPD | 1 | 7.68k 0201 Thin Film Surface Mount Fixed Resistor +/-0.5% 0.031W CPF0201D7K68C1 | READ_DATASHEET | BUY_PART | R0201 | 10k | YAGEO | RC0201FR-0710KL | LCSC | C106225 | Top | https://www.yageo.com/upload/media/product/products/datashee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 | https://jlcpcb.com/partdetail/C106225
R_TYPE_SEL | 1 | 7.68k 0201 Thin Film Surface Mount Fixed Resistor +/-0.5% 0.031W CPF0201D7K68C1 |  |  | R0201 | 2.2000000000000002 |  |  |  |  | Top
R1_EP_DR' | 1 | 7.68k 0201 Thin Film Surface Mount Fixed Resistor +/-0.5% 0.031W CPF0201D7K68C1 |  |  | R0201 | 0.47 |  |  |  |  | Top
R1_USB, R2_USB | 2 | 7.68k 0201 Thin Film Surface Mount Fixed Resistor +/-0.5% 0.031W CPF0201D7K68C1 |  |  | R0201 | 5K1 |  |  |  |  | Top
R2, R3, R4 | 3 | 7.68k 0201 Thin Film Surface Mount Fixed Resistor +/-0.5% 0.031W CPF0201D7K68C1 |  |  | R0201 | 0 |  |  |  |  | Top
R2_EP_DR, R5, R7, R8 | 4 | 7.68k 0201 Thin Film Surface Mount Fixed Resistor +/-0.5% 0.031W CPF0201D7K68C1 | READ_DATASHEET | BUY_PART | R0201 | 10K | YAGEO | RC0201FR-0710KL | LCSC | C106225 | Top | https://www.yageo.com/upload/media/product/products/datashee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 | https://jlcpcb.com/partdetail/C106225
R9 | 1 | 7.68k 0201 Thin Film Surface Mount Fixed Resistor +/-0.5% 0.031W CPF0201D7K68C1 | READ_DATASHEET | BUY_PART | CPF0201D7K68C1_0201 | 10k | YAGEO | RC0201FR-0710KL | LCSC | C106225 | Top | https://www.yageo.com/upload/media/product/products/datashee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 | https://jlcpcb.com/partdetail/C106225
R17, R18 | 2 | 7.68k 0201 Thin Film Surface Mount Fixed Resistor +/-0.5% 0.031W CPF0201D7K68C1 |  |  | R0201 | 3K3 |  |  |  |  | Top
SJ1 | 1 | SMD solder JUMPER |  |  | JUMPER_SJ |  |  |  |  |  | Top
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
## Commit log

2026-04-10 README and folder structure
2026-04-10 Add GNU GPL v3 license
    Added the GNU General Public License version 3 to the project.
2026-04-10 project files uploaded
2026-04-10 Images
2026-04-20 modified README
    Added detailed hardware description and block diagram for InkTime smartwatch.
2026-04-21 resolved all issues
2026-04-21 Update README with hardware details and pinout
    Added detailed hardware description and pinout for nRF52840.

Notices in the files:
parts and their libraries:
COPYRIGHT: Copyright (C) 2024 Ultra Librarian. All rights reserved.
COPYRIGHT: Copyright (C) 2025 Ultra Librarian. All rights reserved.
